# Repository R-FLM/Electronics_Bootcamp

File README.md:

# 42uino mini — Bootcamp Électronique : Design

Carte de développement compatible Arduino (format Pro Mini) à base d'ATmega328P cadencé à 16 MHz, conçue sous KiCad avec des bibliothèques de symboles et d'empreintes personnalisées, selon les règles de fabrication JLCPCB.

| Livrable | Fichier |
|---|---|
| Bibliothèque de symboles | [First_lib.kicad_sym](First_kicad_proj/First_lib.kicad_sym) |
| Bibliothèque d'empreintes | [first_fp_lib.pretty/](First_kicad_proj/first_fp_lib.pretty) |
| Schéma | [First_kicad_proj.kicad_sch](First_kicad_proj/First_kicad_proj.kicad_sch) |
| Layout PCB | [First_kicad_proj.kicad_pcb](First_kicad_proj/First_kicad_proj.kicad_pcb) |
| Export PDF du schéma | [Bootcamp_elec_flomulle_schematic.pdf](First_kicad_proj/Bootcamp_elec_flomulle_schematic.pdf) |
| Export PDF du PCB | [Bootcamp_elec_flomulle_pcb_layout.pdf](First_kicad_proj/Bootcamp_elec_flomulle_pcb_layout.pdf) |

## Nomenclature (BOM)

17 composants. Les liens renvoient aux fiches produit Mouser référencées dans chaque empreinte, d'où l'on accède à la datasheet.

| Réf. | Qté | Valeur | Boîtier | Référence fabricant | Rôle | Datasheet |
|---|---|---|---|---|---|---|
| U1 | 1 | ATmega328P-AN | TQFP-32 | Microchip ATMEGA328P-AN | Microcontrôleur | [Mouser](https://www.mouser.fr/en/ProductDetail/Microchip-Technology/ATMEGA328P-AN?qs=6Dg1WZIWLC6WK556tw8xAw%3D%3D) |
| Y1 | 1 | 16 MHz | 3225 (4 pads) | Kyocera AVX CX3225SA16000D0PSTZ1 | Quartz d'horloge | [Mouser](https://www.mouser.fr/en/ProductDetail/KYOCERA-AVX/CX3225SA16000D0PSTZ1?qs=DN1kgsm7Y2SRgzHPt1S5hg%3D%3D) |
| C1, C2 | 2 | 12 pF | 0603 | Murata GRM1885C2E120FW07J | Capacités de charge du quartz | [Mouser](https://www.mouser.fr/en/ProductDetail/Murata-Electronics/GRM1885C2E120FW07J?qs=d0WKAl%252BL4KbD%2Ff0qK%252BVCeQ%3D%3D) |
| C3, C4, C7 | 3 | 100 nF | 0603 | Vishay Vitramon GA0603Y104MBXAR31G | C3 : filtrage AREF · C4 : auto-reset (DTR → RST) · C7 : découplage VCC | [Mouser](https://www.mouser.fr/en/ProductDetail/Vishay-Vitramon/GA0603Y104MBXAR31G?qs=uwxL4vQweFMKFiCe6YWxnw%3D%3D) |
| C6 | 1 | 1 µF | 0603 | Taiyo Yuden MSASE168SB5105KTNA01 | Découplage VCC | [Mouser](https://www.mouser.fr/en/ProductDetail/TAIYO-YUDEN/MSASE168SB5105KTNA01?qs=yc9RBI4tIAKZAWDraq01Cw%3D%3D) |
| R1 | 1 | 330 Ω | 0603 | Royalohm 0603WAF3300T5E | Limitation de courant de la LED D1 | [Mouser](https://www.mouser.fr/en/ProductDetail/Royalohm/0603WAF3300T5E?qs=sGAEpiMZZMtlubZbdhIBIDH%2FP7BvsepRJZVZEYBKqDw%3D) |
| R2, R3 | 2 | 10 kΩ | 0603 | Littelfuse TFR0603BHC1002NR | R2 : limitation de courant de la LED D2 · R3 : pull-up de RESET | [Mouser](https://www.mouser.fr/en/ProductDetail/Littelfuse/TFR0603BHC1002NR?qs=wT7LY0lnAe3f1NNuny8WOw%3D%3D) |
| D1 | 1 | Verte | 0603 | Lumex SML-LX0603SGW-TR | LED utilisateur sur D13 (SCK) | [Mouser](https://www.mouser.fr/en/ProductDetail/Lumex/SML-LX0603SGW-TR?qs=sGAEpiMZZMvVL5Kk7ZYykWS6taeFwoCBY0eyA%252B5ssLk%3D) |
| D2 | 1 | Rouge | 0603 | Lumex SML-LX0603IW-TR | Témoin d'alimentation | [Mouser](https://www.mouser.fr/en/ProductDetail/Lumex/SML-LX0603IW-TR?qs=sGAEpiMZZMvVL5Kk7ZYykVwAM0Y%252B7BnPfXWhOQRjJ7w%3D) |
| SW1 | 1 | B3U-1000P | SMD | B3U-1000P | Bouton RESET | [Mouser](https://www.mouser.fr/en/ProductDetail/Aratas/B3U-1000P?qs=AO7BQMcsEu4ip80xyf2FwA%3D%3D) |
| J1, J2 | 2 | 1×12 | THT 2,54 mm, droit | TE Connectivity 1-826629-2 | Barrettes d'E/S latérales | [Mouser](https://www.mouser.fr/en/ProductDetail/TE-Connectivity/1-826629-2?qs=FazuUmncXokmxpv%252BFZO3KQ%3D%3D) |
| J3 | 1 | 1×06 | THT 2,54 mm, coudé | Amphenol FCI 10129379-906002BLF | Connecteur de programmation FTDI | [Mouser](https://www.mouser.fr/en/ProductDetail/Amphenol-FCI/10129379-906002BLF?qs=0lQeLiL1qyajiejozaUUsw%3D%3D) |

## Brochage (pinout)

### J1 — barrette 1×12

| Broche | Signal | ATmega (port / broche, fonctions alternatives) | Fonction |
|---|---|---|---|
| 1 | D9 | PB1 / 13 (PCINT1/OC1A) | E/S numérique, PWM |
| 2 | D8 | PB0 / 12 (PCINT0/CLKO/ICP1) | E/S numérique |
| 3 | D7 | PD7 / 11 (PCINT23/AIN1) | E/S numérique |
| 4 | D6 | PD6 / 10 (PCINT22/OC0A/AIN0) | E/S numérique, PWM |
| 5 | D5 | PD5 / 9 (PCINT21/OC0B/T1) | E/S numérique, PWM |
| 6 | D4 | PD4 / 2 (PCINT20/XCK/T0) | E/S numérique |
| 7 | D3 | PD3 / 1 (PCINT19/OC2B/INT1) | E/S numérique, PWM, INT1 |
| 8 | D2 | PD2 / 32 (PCINT18/INT0) | E/S numérique, INT0 |
| 9 | GND | GND / 3, 5, 21 | Masse |
| 10 | RST | PC6 / 29 (RESET/PCINT14) | Reset (actif bas) |
| 11 | RXI | PD0 / 30 (PCINT16/RXD) | UART RX |
| 12 | TXO | PD1 / 31 (PCINT17/TXD) | UART TX |

### J2 — barrette 1×12

| Broche | Signal | ATmega (port / broche, fonctions alternatives) | Fonction |
|---|---|---|---|
| 1 | RAW | VCC / 4, 6 · AVCC / 18 | Alimentation 5 V |
| 2 | GND | GND / 3, 5, 21 | Masse |
| 3 | RST | PC6 / 29 (RESET/PCINT14) | Reset (actif bas) |
| 4 | RAW | VCC / 4, 6 · AVCC / 18 | Alimentation 5 V |
| 5 | A3 | PC3 / 26 (ADC3/PCINT11) | Entrée analogique / E/S |
| 6 | A2 | PC2 / 25 (ADC2/PCINT10) | Entrée analogique / E/S |
| 7 | A1 | PC1 / 24 (ADC1/PCINT9) | Entrée analogique / E/S |
| 8 | A0 | PC0 / 23 (ADC0/PCINT8) | Entrée analogique / E/S |
| 9 | SCK (D13) | PB5 / 17 (PCINT5/SCK) | SPI SCK, LED verte D1 |
| 10 | MISO (D12) | PB4 / 16 (PCINT4/MISO) | SPI MISO |
| 11 | MOSI (D11) | PB3 / 15 (PCINT3/OC2A/MOSI) | SPI MOSI, PWM |
| 12 | D10 | PB2 / 14 (PCINT2/SS/OC1B) | E/S numérique, PWM, SPI SS |

### J3 — connecteur FTDI 1×06

| Broche | Signal | ATmega (port / broche, fonctions alternatives) |
|---|---|---|
| 1 | DTR | PC6 / 29 (RESET/PCINT14), via C4 |
| 2 | TXO | PD1 / 31 (PCINT17/TXD) |
| 3 | RXI | PD0 / 30 (PCINT16/RXD) |
| 4 | RAW | VCC / 4, 6 · AVCC / 18 |
| 5 | GND | GND / 3, 5, 21 |
| 6 | GND | GND / 3, 5, 21 |

### Broches de l'ATmega sans connections
- PC4 / 27 (ADC4/SDA/PCINT12) et PC5 / 28 (ADC5/SCL/PCINT13), soit A4/A5 et donc le bus I²C ;
- ADC6 / 19 et ADC7 / 22, soit A6/A7 ;
- PB6 / 7 (PCINT6/XTAL1/TOSC1) et PB7 / 8 (PCINT7/XTAL2/TOSC2), occupées par le quartz Y1.

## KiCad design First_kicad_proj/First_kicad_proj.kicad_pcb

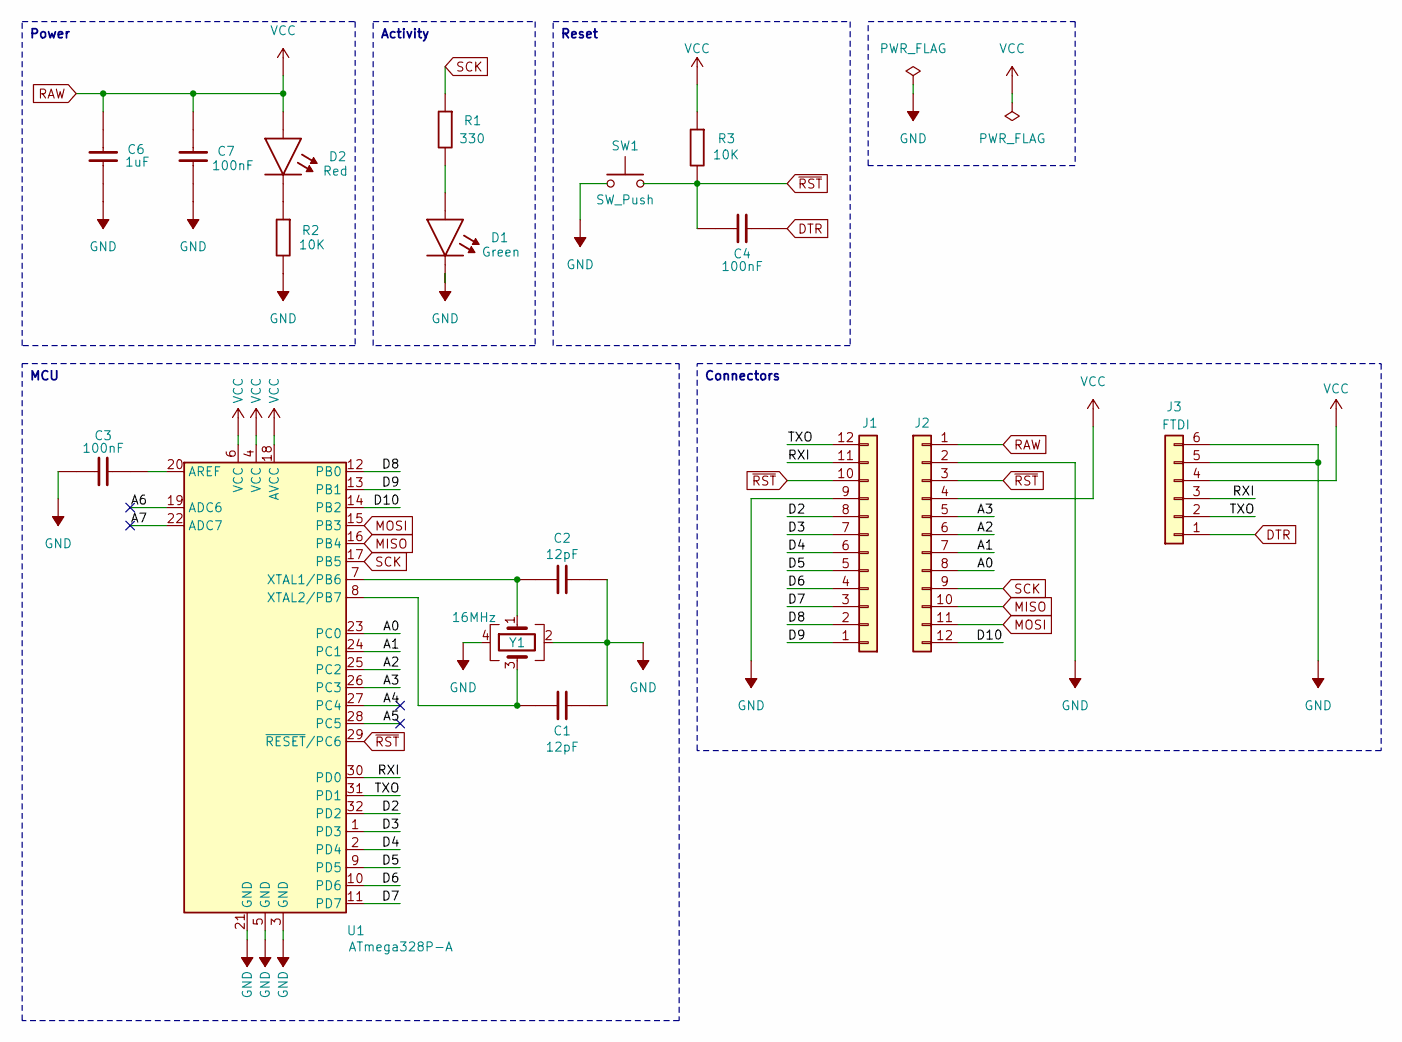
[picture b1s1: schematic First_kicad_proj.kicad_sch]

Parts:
C1, C2: 12pF; C_0603_1608M_12pF
C3, C4, C7: 100nF; C_0603_1608M_100nF
C6: 1uF; C_0603_1608M_1uF
D1: Green; LED_0603_1608M_GREEN
D2: Red; LED_0603_1608M_RED
J1, J2: J; Connectors_PIN_1x12_2.54_Vectical
J3: FTDI; Connectors_PIN_1x06_2.54_Horizontal
R1: 330; R_0603_1608M_330
R2, R3: 10K; R_0603_1608M_10K
SW1: SW_Push; SW_SPST_B3U_1000P
U1: ATmega328P-A; MCU_TQFP_ATmega328P-AN
Y1: 16MHz; Crystal_3225_16MHz

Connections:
/A0: J2.8, U1.23 (PC0)
/A1: J2.7, U1.24 (PC1)
/A2: J2.6, U1.25 (PC2)
/A3: J2.5, U1.26 (PC3)
/A4: U1.27 (PC4)
/A5: U1.28 (PC5)
/A6: U1.19 (ADC6)
/A7: U1.22 (ADC7)
/D2: J1.8, U1.32 (PD2)
/D3: J1.7, U1.1 (PD3)
/D4: J1.6, U1.2 (PD4)
/D5: J1.5, U1.9 (PD5)
/D6: J1.4, U1.10 (PD6)
/D7: J1.3, U1.11 (PD7)
/D8: J1.2, U1.12 (PB0)
/D9: J1.1 (PIN_1), U1.13 (PB1)
/D10: J2.12, U1.14 (PB2)
/RXI: J1.11, J3.3, U1.30 (PD0)
/TXO: J1.12, J3.2, U1.31 (PD1)
DTR: C4.2, J3.1
GND: C1.2, C2.2, C3.1, C6.2, C7.2, D1.1 (K), J1.9, J2.2, J3.5, J3.6, R2.2, SW1.1, U1.3 (GND), U1.5 (GND), U1.21 (GND), Y1.2 (GND), Y1.4 (GND)
MISO: J2.10, U1.16 (PB4)
MOSI: J2.11, U1.15 (PB3)
unnamed: D1.2 (A), R1.2
unnamed: D2.1 (K), R2.1
unnamed: C3.2, U1.20 (AREF)
unnamed: C2.1, U1.7 (XTAL1/PB6), Y1.1
unnamed: C1.1, U1.8 (XTAL2/PB7), Y1.3
RAW: C6.1, C7.1, D2.2 (A), J2.1 (PIN_1), J2.4, J3.4, R3.1, U1.4 (VCC), U1.6 (VCC), U1.18 (AVCC)
RST: C4.1, J1.10, J2.3, R3.2, SW1.2, U1.29 (~RESET/PC6)
SCK: J2.9, R1.1, U1.17 (PB5)

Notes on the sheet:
MCU
Power
Activity
Reset
Connectors

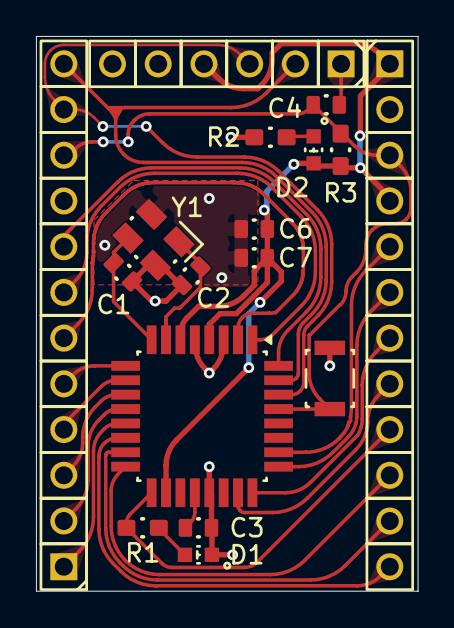
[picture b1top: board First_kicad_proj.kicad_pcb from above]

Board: 2 copper layers, 21.2 x 30.8 mm, 17 parts (0 on the bottom side), 27 nets.
